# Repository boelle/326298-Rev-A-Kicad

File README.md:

Shield: [![CC BY-NC-ND 4.0][cc-by-nc-nd-shield]][cc-by-nc-nd]

This work is licensed under a [Attribution-NonCommercial-NoDerivatives 4.0 International License][cc-by-nc-nd].

[![CC BY-NC-ND 4.0][cc-by-nc-nd-image]][cc-by-nc-nd]

[cc-by-nc-nd]: http://creativecommons.org/licenses/by-nc-nd/4.0/
[cc-by-nc-nd-image]: https://licensebuttons.net/l/by-nc-nd/4.0/88x31.png
[cc-by-nc-nd-shield]: https://img.shields.io/badge/License-CC%20BY--NC--ND%204.0-lightgrey.svg

# What is this?

It's my project/attempt at recreating the first board used in C64 production.
It's based on a schematic by Ruud Baltissen.

# How?
I got one of these boards without much components, all chips where gone (almost).
I then removed the rest and cleaned out all holes and got it scanned at a local copy shop.
Initial I used sprint layout which has a feature to trace on top of an image.
But I wanted a more "complete" soloution so I imported the copper layers in to kicad and 
managed to trace on top of that. 
But the schematic was not the same as the board and I got help from Fredric QJ Blåholtz
adjustning the schematic to the board, it's a bit backwards but I trust the board more.

# Why?
I have been asked that a lot. One reason is that I have always liked the C64 and I
wanted to get more intimate with it. One thing I have truly learned is that QA and QC 
was not that much used 37 years ago, anything that worked was ok. So boards could differ 
even thou they had the same number. So I decided to just stick with making a replica of
what I had. 

The other reason is that I have a lot of time on my hands so I wanted to make
something, that at some point will come in as usefull. These boards will at some point fail.
They where not robust made 37 years ago and either a hole will break loose from the board
or a track will crack. Having a source for a new board would then come in handy. Simply
pick a PCB house that you trust and send them the gerber files. Most have a minimum order
so you will never have a problem again.

# Status?
I have verified the board by printing out the tracks on paper and used a needle to poke
through and see if things match up. It does very close but since paper under the real board
can move it will not be precise, but it's as good as I can do it.

I have also added some "eyecandy" in the form of 3d shapes of most things on the board. 
there are some things I can't find thou and my skills are not up to doing that from scratch,
but if anyone wants to chip in I need step/stp files for these parts:

# Plan?
At summer 2020 I will order 5 boards as that is the minimum from Elecrow. I will then
during fall/winter buy and add components. Since the chips are the most expensive parts,
it might be as far as early 2021 before i can power it up

# Working on right now?
Trying to locate cad/3d models in step/stp format for the missing bits

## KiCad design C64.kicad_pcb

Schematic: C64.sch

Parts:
C1, C2, C3, C16, C18, C22, C30, C31, C32, C35, C39, C45, C46, C47, C55, C56, C58, C68, C71, C74, C76, C77, C82, C84, C87, C89, C95, C96: 0.1 uF; 12_03_07
C4, C5, C6, C7, C9, C29, C33, C44, C51, C60, C85: 0.47 uF; 12_03_07
C8, C12, C13, C14, C15, C17, C24, C34, C57, C62, C64, C65, C94: 10 uF 25V; CAPACITOR_ELECTROLYTIC_2.5_6
C10, C11: 2200 pF Polyester; polyester12_03_07
C19: 2200 uF 16V; E37-31.5-17.5-E
C20, C21, C97, C98, C99, C100: 0.22 uF 100V; 0203
C23: 360 pF; 12_03_07
C25, C26, C27, C28, C40, C41, C42, C43, C50, C54, C59, C92: 0.22 uF; 12_03_07
C36: 20 pF 50V; 12_03_07
C37, C48, C93: 1000 pF; 12_03_07
C38, C80: 51 pF; 12_03_07
C49, C52: 470 pF 50V; 12_03_07
C53: 470 pF; 12_03_07
C61, C63, C66, C67: 0.47 uF 50V 20%; 15_4_10
C70: 10 pF 5%; 12_03_07
C72, C78: 220 pF 50V; 12_03_07
C73: 150 pF 50V; 12_03_07
C79: 510 pF; 12_03_07
C81: 20 pF; 12_03_07
C83: 33 pF; 12_03_07
C86: 39 pF 50V 5%; 12_03_07
C88, C90: 470 uF 50V; E37-31.5-17.5-E
C91: 100 uF 16V; C_E_5-9
C101: 0.1 uF; P5
CN1: KEYBOARD; 20way
CN2: USERPORT
CN3: CASSETTEPORT
CN4: DIN6
CN5: DIN5
CN6: EXPANSIONPORT
CN7: DIN7
CN8, CN9: CONTROL_PORT
CR1: 1N4371 2.7 V; D-12_3_7
CR2: 7.5 V; D-12_3_7
CR3: 1N914; D-12_3_7
CR4: BRIDGE_RECTIFIER
CR5, CR6: 1N4001; D-12_3_7
F1: 1A; SH32
FB1, FB2, FB3, FB4, FB5, FB6, FB7, FB8, FB9, FB10, FB11, FB12, FB13, FB14, FB15, FB16, FB17, FB18: FERRITE_BEAD
FRAME1: FRAME_D_L
J1, J2, J3: Conn_01x01; Socket_Strip_Straight_1x01_Pitch2.54mm
JP2E1: CN10; 3way
L1, L2: 2.2 uH; 12_03_07
L3: 3 uH; 12_03_07
L4: LINEFILTER
L5: 1.2 uH; P15
Q1: 2N4401; TO92
Q2: 2N3904; TO92
Q3: TIP29B
Q4, Q5, Q6, Q7, Q8: PN2222; TO92
R1, R24, R43, R44, R45: 3.3 K; 12_03_07
R2, R5, R15, R22: 1.5 K; 12_03_07
R3, R7: 10 K; 12_03_07
R4, R6, R13, R16, R23, R28, R29, R30, R31, R36, R38: 1 K; 12_03_07
R8, R39: 390; 12_03_07
R9, R26: 75; 12_03_07
R10, R11: 120; 12_03_07
R14: 100; 12_03_07
R17: 1.2 K; 12_03_07
R18: 230; 12_03_07
R19: 15 K; 12_03_07
R20, R37: 6.8 K; 12_03_07
R21: 4.7 K; 12_03_07
R25: 1 K Trim Pot; POT_METER
R27: 2 K Trim Pot; POT_METER
R33, R34: 47 K; 12_03_07
R35: 470 K; 12_03_07
R41: 1 M; 12_03_07
R42: 0; 12_03_07
R46: 2.1 K; 12_03_07
R49: 470; 12_03_07
RF1: RF-MODULATOR
RP1, RP2: 33; RESISTOR_PACK_4
RP3: 3.3 K; RESISTOR_PACK_4
RP4: 3.3 K; RESISTOR_PACK_9
SW1: DPDT_SWITCH
U1, U2: 6526
U3, U4: 2364
U5: 2332
U6: 2114
U7: 6510
U8: SN7406NN
U9, U10, U11, U12, U21, U22, U23, U24: 4164
U13, U25: SN74257N
U14: SN74258N
U15: SN74139N
U16, U28: 4066
U17: C64PLA
U18: 6581
U19: 6569
U20: 556DIGITAL
U26: SN74373N; 74373N
U27: SN7408N
U29: SN7474N
U30: SN74193N
U31: SN74629
U32: MC4044
U33: 74LS02; 7402
U34: 74LS175; SN74629
VR1: 7812; VR
VR2: 7805; VR
Y1: 17.73 MHz; HC49TL-H

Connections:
/+5Vc: C55.1, C56.1, C67.1, C68.1, C74.1, C82.1, C84.1, J1.1, L2.2, Q7.3 (C), R16.1, R23.1, R26.1, R27.E, U29.10 (PRE), U29.13 (CLR), U29.14 (VCC), U30.4 (CNT-DWN), U30.15 (A), U30.16 (VCC), U31.16 (VCC), U32.14 (VCC)
/+5Vcan: C60.1, C63.1, C64.+ (1), C65.+ (1), C66.1, C101.1, L1.1, L2.1, U19.40 (VCC), VR2.3 (VO)
/+5Vvid: C61.1, C71.1, C77.1, L1.2, Q4.3 (C), Q5.3 (C), R8.1, R13.1
/+9V: C18.1, C19.+ (1), C95.1, CR4.1 (+), CR6.1 (A), Q1.3 (C), Q3.2 (C), R2.1, VR2.1 (VI)
/+12V: C52.1, C53.1, C57.+ (1), C59.1, C62.+ (1), C94.+ (1), FB11.1, FB12.1, Q8.3 (C), VR1.3 (VO)
/A0: CN6.Y (A0), U1.38 (RS0), U2.38 (RS0), U3.8 (A0), U4.8 (A0), U5.8 (A0), U6.5 (A0), U7.7 (A0), U18.9 (A0), U25.13 (4B), U26.6 (3Q)
/A1: CN6.X (A1), U1.37 (RS1), U2.37 (RS1), U3.7 (A1), U4.7 (A1), U5.7 (A1), U6.6 (A1), U7.8 (A1), U18.10 (A1), U25.10 (3B), U26.12 (5Q)
/A2: CN6.W (A2), U1.36 (RS2), U2.36 (RS2), U3.6 (A2), U4.6 (A2), U5.6 (A2), U6.7 (A2), U7.9 (A2), U18.11 (A2), U25.6 (2B), U26.9 (4Q)
/A3: CN6.V (A3), U1.35 (RS3), U2.35 (RS3), U3.5 (A3), U4.5 (A3), U5.5 (A3), U6.4 (A3), U7.10 (A3), U18.12 (A3), U25.3 (1B), U26.15 (6Q)
/A4: CN6.U (A4), U3.4 (A4), U4.4 (A4), U5.4 (A4), U6.3 (A4), U7.11 (A4), U13.13 (4B), U18.13 (A4), U26.16 (7Q)
/A5: CN6.T (A5), U3.3 (A5), U4.3 (A5), U5.3 (A5), U6.2 (A5), U7.12 (A5), U13.6 (2B), U26.19 (8Q)
/A6: CN6.S (A6), U3.2 (A6), U4.2 (A6), U5.2 (A6), U6.1 (A6), U7.13 (A6), U13.3 (1B), U26.5 (2Q)
/A7: CN6.R (A7), U3.1 (A7), U4.1 (A7), U5.1 (A7), U6.17 (A7), U7.14 (A7), U26.2 (1Q)
/A8: CN6.P (A8), U3.23 (A8), U4.23 (A8), U5.23 (A8), U6.16 (A8), U7.15 (A8), U15.14 (A), U19.32 (A8), U25.14 (4A)
/A9: CN6.N (A9), U3.22 (A9), U4.22 (A9), U5.22 (A9), U6.15 (A9), U7.16 (A9), U15.13 (B), U19.33 (A9), U25.11 (3A)
/A10: CN6.M (A10), U3.19 (A10), U4.19 (A10), U5.19 (A10), U7.17 (A10), U15.2 (A), U19.34 (A10), U25.5 (2A)
/A11: CN6.L (A11), U3.18 (A11), U4.18 (A11), U5.18 (A11), U7.18 (A11), U15.3 (B), U19.23 (A11), U25.2 (1A)
/A12: CN6.K (A12), RP4.9 (X), U3.21 (A12), U4.21 (A12), U7.19 (A12), U13.14 (4A), U17.27 (A12)
/A13: CN6.J (A13), RP4.7 (X), U7.20 (A13), U13.5 (2A), U17.2 (A13)
/A14: CN6.H (A14), RP4.5 (X), U7.22 (A14), U13.2 (1A), U17.3 (A14)
/A15: CN6.F (A15), RP4.4 (X), U7.23 (A15), U13.11 (3A), U17.4 (A15)
/D0: CN6.21 (D0), U1.33 (D0), U2.33 (D0), U3.9 (O0), U4.9 (O0), U5.9 (O0), U7.37 (D0), U16.11 (Y3), U18.15 (D0), U19.7 (D0), U21.2 (DI), U21.14 (DO)
/D1: CN6.20 (D1), U1.32 (D1), U2.32 (D1), U3.10 (O1), U4.10 (O1), U5.10 (O1), U7.36 (D1), U9.2 (DI), U9.14 (DO), U16.8 (Y2), U18.16 (D1), U19.6 (D1)
/D2: CN6.19 (D2), U1.31 (D2), U2.31 (D2), U3.11 (O2), U4.11 (O2), U5.11 (O2), U7.35 (D2), U16.4 (Y1), U18.17 (D2), U19.5 (D2), U22.2 (DI), U22.14 (DO)
/D3: CN6.18 (D3), U1.30 (D3), U2.30 (D3), U3.13 (O3), U4.13 (O3), U5.13 (O3), U7.34 (D3), U10.2 (DI), U10.14 (DO), U16.1 (Y0), U18.18 (D3), U19.4 (D3)
/D4: CN6.17 (D4), U1.29 (D4), U2.29 (D4), U3.14 (O4), U4.14 (O4), U5.14 (O4), U7.33 (D4), U18.19 (D4), U19.3 (D4), U23.2 (DI), U23.14 (DO)
/D5: CN6.16 (D5), U1.28 (D5), U2.28 (D5), U3.15 (O5), U4.15 (O5), U5.15 (O5), U7.32 (D5), U11.2 (DI), U11.14 (DO), U18.20 (D5), U19.2 (D5)
/D6: CN6.15 (D6), U1.27 (D6), U2.27 (D6), U3.16 (O6), U4.16 (O6), U5.16 (O6), U7.31 (D6), U18.21 (D6), U19.1 (D6), U24.2 (DI), U24.14 (DO)
/D7: CN6.14 (D7), U1.26 (D7), U2.26 (D7), U3.17 (O7), U4.17 (O7), U5.17 (O7), U7.30 (D7), U12.2 (DI), U12.14 (DO), U18.22 (D7), U19.39 (D7)
/IRQ: CN6.4 (IRQ), RP4.2, U1.21 (~IRQ~), U7.3 (~IRQ~), U19.8 (~IRQ~)
/MA0: RP2.4 (2), U9.5 (A0), U10.5 (A0), U11.5 (A0), U12.5 (A0), U21.5 (A0), U22.5 (A0), U23.5 (A0), U24.5 (A0)
/MA1: RP2.8 (2), U9.7 (A1), U10.7 (A1), U11.7 (A1), U12.7 (A1), U21.7 (A1), U22.7 (A1), U23.7 (A1), U24.7 (A1)
/MA2: RP2.6 (2), U9.6 (A2), U10.6 (A2), U11.6 (A2), U12.6 (A2), U21.6 (A2), U22.6 (A2), U23.6 (A2), U24.6 (A2)
/MA3: RP2.2, U9.12 (A3), U10.12 (A3), U11.12 (A3), U12.12 (A3), U21.12 (A3), U22.12 (A3), U23.12 (A3), U24.12 (A3)
/MA4: RP1.4 (2), U9.11 (A4), U10.11 (A4), U11.11 (A4), U12.11 (A4), U21.11 (A4), U22.11 (A4), U23.11 (A4), U24.11 (A4)
/MA5: RP1.6 (2), U9.10 (A5), U10.10 (A5), U11.10 (A5), U12.10 (A5), U21.10 (A5), U22.10 (A5), U23.10 (A5), U24.10 (A5)
/MA6: RP1.2, U9.13 (A6), U10.13 (A6), U11.13 (A6), U12.13 (A6), U21.13 (A6), U22.13 (A6), U23.13 (A6), U24.13 (A6)
/MA7: RP1.8 (2), U9.9 (A7), U10.9 (A7), U11.9 (A7), U12.9 (A7), U21.9 (A7), U22.9 (A7), U23.9 (A7), U24.9 (A7)
/N$1: C12.+ (1), C35.1, U18.26 (EXT-IN)
/N$2: FB13.1, R6.1, U18.27 (AUDIO-OUT)
/N$3: FB13.2, R7.1
/N$4: C37.1, Q8.2 (B), R7.2
/N$5: C13.+ (1), Q8.1 (E), R38.1
/N$6: C10.2, U18.2 (CAP1B)
/N$7: C11.2, U18.4 (CAP2B)
/N$8: C10.1, U18.1 (CAP1A)
/N$9: C11.1, U18.3 (CAP2A)
/N$10: C13.- (2), CN5.3, RF1.AUDI (AUDIO)
/N$11: C12.- (2), CN5.5
/N$12: C34.+ (1), C50.1, FB10.1, R46.1, U18.25 (VCC)
/N$13: C16.1, FB6.2, RF1.+ (+V)
/N$14: C51.1, FB11.2, U18.28 (V12)
/N$15: C80.1, FB14.2, R25.A
/N$16: FB14.1, U19.14 (COLOR)
/N$17: C97.1, CN7.4, CN7.5, L5.1
/N$18: C100.1, L5.2, SW1.2
/N$19: C20.2, CN7.6, L4.4
/N$20: C20.1, CN7.7, L4.2
/N$21: C21.1, C98.1, F1.1A, F1.1B, L4.3
/N$22: C21.2, C99.1, L4.1, SW1.5
/N$23: CN2.11 (9VAC1), CR4.4 (AC2), F1.2A, F1.2B, R5.1
/N$24: C90.- (2), CN2.10 (9VAC2), CR4.3 (AC1), SW1.6 (O)
/N$26: C90.+ (1), CR5.1 (A), CR6.2 (C)
/N$27: C88.+ (1), C89.1, CR5.2 (C), VR1.1 (VI)
/N$28: R24.1, R25.S
/N$29: C81.2, R24.2
/N$30: C81.1, Q6.2 (B), R20.1, R21.1
/N$31: Q5.2 (B), Q6.3 (C), R13.2, R20.2
/N$32: C79.2, Q5.1 (E), R14.1
/N$33: L3.1, R10.2, R11.2, R18.1
/N$35: C54.1, FB12.2, U19.13 (V12)
/N$36: C73.1, CR3.1 (A), Q4.2 (B), R8.2
/N$37: CR3.2 (C), FB15.2
/N$38: Q4.1 (E), R9.1, R10.1
/N$39: C72.1, CN5.1, R9.2
/N$41: C78.1, CN5.4, L3.2, R49.1, RF1.VIDE (VIDEO)
/N$42: U14.10 (3B), U14.11 (3A), U19.31 (A7)
/N$44: U14.13 (4B), U14.14 (4A), U19.30 (A6)
/N$45: U14.3 (1B), U14.12 (4Y)
/N$46: U14.6 (2B), U14.9 (3Y)
/N$47: U6.14 (D0), U16.10 (Z3), U19.38 (D8)
/N$48: U6.13 (D1), U16.9 (Z2), U19.37 (D9)
/N$49: U6.12 (D2), U16.3 (Z1), U19.36 (D10)
/N$50: U6.11 (D3), U16.2 (Z0), U19.35 (D11)
/N$51: R42.2, U17.18 (CASRAM)
/N$52: U8.11 (I), U14.15 (G), U16.5 (E1), U16.6 (E2), U16.12 (E3), U16.13 (E0), U19.16 (AEC), U26.1 (OC), U27.4 (I0), U27.10 (I1)
/N$53: U8.13 (I), U13.1 (~A~/B), U14.1 (~A~/B), U17.9 (CAS), U19.19 (~CAS~), U25.1 (~A~/B)
/N$54: R42.1, U9.15 (~CAS), U10.15 (~CAS), U11.15 (~CAS), U12.15 (~CAS), U21.15 (~CAS), U22.15 (~CAS), U23.15 (~CAS), U24.15 (~CAS)
/N$55: U9.4 (~RAS), U10.4 (~RAS), U11.4 (~RAS), U12.4 (~RAS), U19.18 (~RAS~), U21.4 (~RAS), U22.4 (~RAS), U23.4 (~RAS), U24.4 (~RAS), U26.11 (ENC)
/N$56: U6.8 (~CS), U27.8 (O)
/N$59: C24.- (2), R34.2, U20.8 (TR), U20.12 (THR)
/N$60: U8.5 (I), U20.5 (Q)
/N$61: C23.1, R33.2, U20.1 (DIS), U20.2 (THR)
/N$62: C38.2, R35.1, U20.6 (TR)
/N$63: C38.1, CN1.3, R41.2
/N$64: R26.2, U31.15 (I1)
/N$65: C58.1, R27.S, U31.1 (VCO)
/N$66: FB16.1, U31.10 (Y1)
/N$67: C70.2, U31.13 (X2)
/N$68: U31.12 (X1), Y1.2
/N$69: C70.1, Y1.1
/N$70: FB16.2, U19.21 (COLCLK), U30.5 (CNT-UP)
/N$71: C83.1, U30.11 (LOAD), U30.12 (CRY)
/N$72: J3.1, U29.4 (PRE), U30.1 (C), U30.10 (B)
/N$73: U29.5 (Q), U30.9 (D)
/N$74: R16.2, R17.2, U31.2 (FREQ), U32.8 (BO)
/N$75: U29.11 (CLK), U30.6 (QC)
/N$76: U29.8 (~Q), U29.12 (D)
/N$77: U32.2 (PDO2), U32.11 (CPI2)
/N$78: U32.4 (CPI1), U32.13 (PDO1)
/N$79: C87.1, R22.1, R23.2, U31.3 (I3)
/N$80: C86.1, U31.4 (C1)
/N$81: C86.2, U31.5 (C2)
/N$82: FB17.1, U31.7 (Y2)
/N$83: U29.9 (Q), U32.1 (PDI1)
/N$84: CN3.5 (WRITE1), CN3.E (WRITE2), FB1.1
/N$85: R19.2, U32.5 (CPI3), U32.10 (CPO)
/N$86: C85.1, R17.1
/N$87: C36.1, CN6.6 (DOTCLK), FB17.2, U19.22 (DOTCLK)
/N$88: C85.2, Q7.2 (B), R19.1
/N$89: R31.2, U8.10 (O), U13.15 (G), U17.25 (AEC), U25.15 (G)
/N$90: Q7.1 (E), U32.9 (BI)
/N$91: CN1.19, CN8.2, U1.3 (PA1)
/N$92: CN1.18, CN8.3, U1.4 (PA2)
/N$93: CN1.17, CN8.4, U1.5 (PA3)
/N$94: CN1.16, CN8.6, U1.6 (PA4)
/N$95: CN1.15, U1.7 (PA5)
/N$96: CN1.14, U1.8 (PA6), U28.6 (E2), U28.12 (E3)
/N$97: CN1.20, U1.9 (PA7), U28.5 (E1), U28.13 (E0)
/N$98: CN1.13, CN8.1, U1.2 (PA0)
/N$99: CN1.12, CN9.1, U1.10 (PB0)
/N$100: CN1.11, CN9.2, U1.11 (PB1)
/N$101: CN1.10, CN9.3, U1.12 (PB2)
/N$102: CN1.9, U1.17 (PB7)
/N$103: CN1.8, CN9.6, U1.14 (PB4), U19.9 (LP)
/N$104: CN1.7, U1.15 (PB5)
/N$105: CN1.5, CN9.4, U1.13 (PB3)
/N$106: CN1.6, U1.16 (PB6)
/N$107: CN8.9, U28.1 (Y0)
/N$108: CN8.5, U28.4 (Y1)
/N$109: CN8.7, CN9.7, FB18.1
/N$110: CN9.9, U28.8 (Y2)
/N$111: CN9.5, U28.11 (Y3)
/N$113: C93.2, U18.23 (POTY), U28.3 (Z1), U28.10 (Z3)
/N$114: CN4.3, FB7.1
/N$115: CN4.4, FB9.1
/N$116: CN4.5, FB8.1
/N$117: FB8.2, R29.2, U2.9 (PA7), U8.4 (O)
/N$118: FB9.2, R30.2, U2.8 (PA6), U8.8 (O)
/N$119: CN2.9 (ATN), FB7.2, R28.2, U8.2 (O)
/N$120: CN2.8 (PC2), U2.18 (~PC~)
/N$121: CN2.L (PB7), U2.17 (PB7)
/N$122: CN2.K (PB6), U2.16 (PB6)
/N$123: CN2.J (PB5), U2.15 (PB5)
/N$124: CN2.H (PB4), U2.14 (PB4)
/N$125: CN2.F (PB3), U2.13 (PB3)
/N$126: CN2.E (PB2), U2.12 (PB2)
/N$127: CN2.D (PB1), U2.11 (PB1)
/N$128: CN2.C (PB0), U2.10 (PB0)
/N$129: CN2.B (FLAG2), RP3.2, U2.24 (~FLAG~)
/N$130: U2.7 (PA5), U8.3 (I)
/N$131: U2.6 (PA4), U8.9 (I)
/N$132: U2.5 (PA3), U8.1 (I)
/N$133: CN3.3 (MOTOR1), CN3.C (MOTOR2), FB2.1
/N$134: CN2.4 (CNT1), RP3.5 (X), U1.40 (CNT)
/N$135: U2.2 (PA0), U14.2 (1A), U17.5 (VIA14)
/N$136: U2.3 (PA1), U14.5 (2A)
/N$137: CN2.M (PA2), U2.4 (PA2)
/N$138: CN2.7 (SP2), RP3.8 (X), U2.39 (SP)
/N$139: CN2.6 (CNT2), RP3.7 (X), U2.40 (CNT)
/N$140: CN2.5 (SP1), RP3.6 (X), U1.39 (SP)
/N$141: FB5.1, U7.39 (CLKOUT)
/N$143: C76.1, R15.1, U31.14 (RNG)
/N$145: U3.20 (CS), U17.17 (BASIC)
/N$146: CR1.2 (C), R5.2, R37.2, U27.12 (I0)
/N$147: R37.1, U1.19 (TOD), U2.19 (TOD), U27.11 (O)
/N$148: JP2E1.1, JP2E1.3, R39.2; also elsewhere on the board
/N$152: U4.20 (CS), U17.16 (KERNAL)
/N$153: CN6.C (RESET), FB4.1
/N$155: CN6.12 (BA), U17.26 (BA), U19.12 (BA), U27.1 (I0), U33.2 (I1), U33.12 (I1)
/N$157: CN6.11 (ROML), U17.11 (ROML)
/N$158: CN6.B (ROMH), U17.10 (ROMH)
/N$159: CN6.9 (EXROM), RP4.8 (X), U17.23 (EXROM)
/N$160: CN6.8 (GAME), RP4.6 (X), U17.22 (GAME)
/N$162: FB15.1, U19.15 (SYNC)
/N$163: U15.4 (Y0), U19.10 (~CS~)
/N$164: R45.2, U7.29 (P0), U17.8 (LORAM)
/N$165: R44.2, U7.28 (P1), U17.7 (HIRAM)
/N$166: R43.2, U7.27 (P2), U17.6 (CHAREN)
/N$167: U7.2 (RDY), U27.3 (O)
/N$168: U7.5 (AEC), U27.6 (O)
/N$169: CN6.13 (DMA), RP4.10 (X), U27.2 (I1), U27.5 (I1)
/N$170: U5.20 (CS1), U17.15 (CHAROM)
/N$171: CN3.4 (READ1), CN3.D (READ2), CN4.1, RP3.4 (X), U1.24 (~FLAG~)
/N$172: CN3.6 (SENSE1), CN3.F (SENSE2), R1.2, U7.25 (P4)
/N$173: C1.1, CN3.2 (VCC1), CN3.B (VCC2), FB3.1
/N$176: FB1.2, U7.26 (P3)
/N$177: Q2.2 (B), R3.1, R4.2
/N$178: Q1.1 (E), Q3.1 (B)
/N$179: C18.2, CR2.2 (C), Q1.2 (B), Q2.3 (C), R2.2
/N$180: FB2.2, Q3.3 (E)
/N$181: R4.1, U7.24 (P5)
/N$182: U1.23 (~CS~), U15.12 (Y0)
/N$183: U2.23 (~CS~), U15.11 (Y1)
/N$184: U6.10 (~WE), U17.13 (GR/W)
/N$185: U15.1 (G), U17.12 (I/O)
/N$186: U15.7 (Y3), U15.15 (G)
/N$187: CN6.7 (IO1), U15.10 (Y2)
/N$188: CN6.10 (IO2), U15.9 (Y3)
/N$189: U15.5 (Y1), U18.8 (CS)
/N$190: U15.6 (Y2), U27.9 (I0)
/NA0: RP2.3 (1), U19.24 (A0/A8), U25.12 (4Y), U26.7 (3D)
/NA1: RP2.7 (1), U19.25 (A1/A9), U25.9 (3Y), U26.13 (5D)
/NA2: RP2.5 (1), U19.26 (A2/A10), U25.7 (2Y), U26.8 (4D)
/NA3: RP2.1, U19.27 (A3/A11), U25.4 (1Y), U26.14 (6D)
/NA4: RP1.3 (1), U13.12 (4Y), U17.20 (VA12), U19.28 (A4/A12), U26.17 (7D)
/NA5: RP1.5 (1), U13.7 (2Y), U17.21 (VA13), U19.29 (A5/A13), U26.18 (8D)
/NA6: RP1.1, U13.4 (1Y), U14.4 (1Y), U26.4 (2D)
/NA7: RP1.7 (1), U13.9 (3Y), U14.7 (2Y), U26.3 (1D)
/NMI: CN6.D (NMI), RP3.3 (X), U2.21 (~IRQ~), U7.4 (~NMI~), U8.6 (O)
/PHI0: U7.1 (CLKIN), U19.17 (PHI0), U32.3 (PDI2), U33.5 (I1)
/PHI2: CN6.E (PHI2), FB5.2, U1.25 (CLKOUT), U2.25 (CLKOUT), U18.6 (CLKOUT)
/RES: CN2.3 (RESET), CN4.6, FB4.2, R36.2, U1.34 (~RES~), U2.34 (~RES~), U7.40 (~RES~), U18.5 (RESET), U20.9 (Q), U20.13 (DIS)
/RW: CN6.5 (R/W), R46.2, RP4.3 (X), U1.22 (R/W), U2.22 (R/W), U7.38 (R/W), U9.3 (~WE), U10.3 (~WE), U11.3 (~WE), U12.3 (~WE), U17.24 (R/W), U18.7 (R/W), U19.11 (~R/W~), U21.3 (~WE), U22.3 (~WE), U23.3 (~WE), U24.3 (~WE)
/VCC: C2.1, C3.1, C4.1, C5.1, C6.1, C7.1, C8.+ (1), C9.1, C14.+ (1), C15.+ (1), C17.+ (1), C22.1, C24.+ (1), C25.1, C26.1, C27.1, C28.1, C29.1, C30.1, C31.1, C32.1, C33.1, C39.1, C40.1, C41.1, C42.1, C43.1, C44.1, C45.1, C46.1, C47.1, C49.1, C91.+ (1), C92.1, C96.1, CN1.4, CN2.2 (VCC), CN6.2 (+5V1), CN6.3 (+5V2), FB3.2, FB6.1, FB10.2, FB18.2, R1.1, R28.1, R29.1, R30.1, R31.1, R33.1, R35.2, R36.1, R39.1, R41.1, R43.1, R44.1, R45.1, RP3.1, RP4.1, SW1.3 (O), U1.20 (VCC), U2.20 (VCC), U3.24 (VCC), U4.24 (VCC), U5.21 (CS2), U5.24 (VCC), U6.18 (VCC), U7.6 (VCC), U8.14 (VCC), U9.8 (VCC), U10.8 (VCC), U11.8 (VCC), U12.8 (VCC), U13.16 (VCC), U14.16 (VCC), U15.16 (VCC), U16.14 (VCC), U17.28 (VCC), U20.4 (R), U20.10 (R), U20.14 (VCC), U21.8 (VCC), U22.8 (VCC), U23.8 (VCC), U24.8 (VCC), U25.16 (VCC), U26.20 (VCC), U27.13 (I1), U27.14 (VCC), U28.14 (VCC), U33.14 (VCC), U34.16
unnamed: C79.1, R18.2
unnamed: U33.1 (I0), U34.1 (~Mr), U34.4 (D0)
unnamed: U33.4 (I0), U33.9 (I1), U34.9 (Cp)
unnamed: U33.11 (O), U34.11 (~Q2)
unnamed: U33.8 (O), U33.13 (I0)
unnamed: U34.2 (Q0), U34.5 (D1)
unnamed: U34.7 (Q1), U34.12 (D2)

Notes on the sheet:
Based on schematic done by Ruud Baltissen. Values and footprints corrected by Bo Herrmannsen Help with correcting schematic to match board by Fredric QJ Blåholtz
20-02-2018
Commodore C64 Rev A Replica Schematic
? Ends blind on board

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
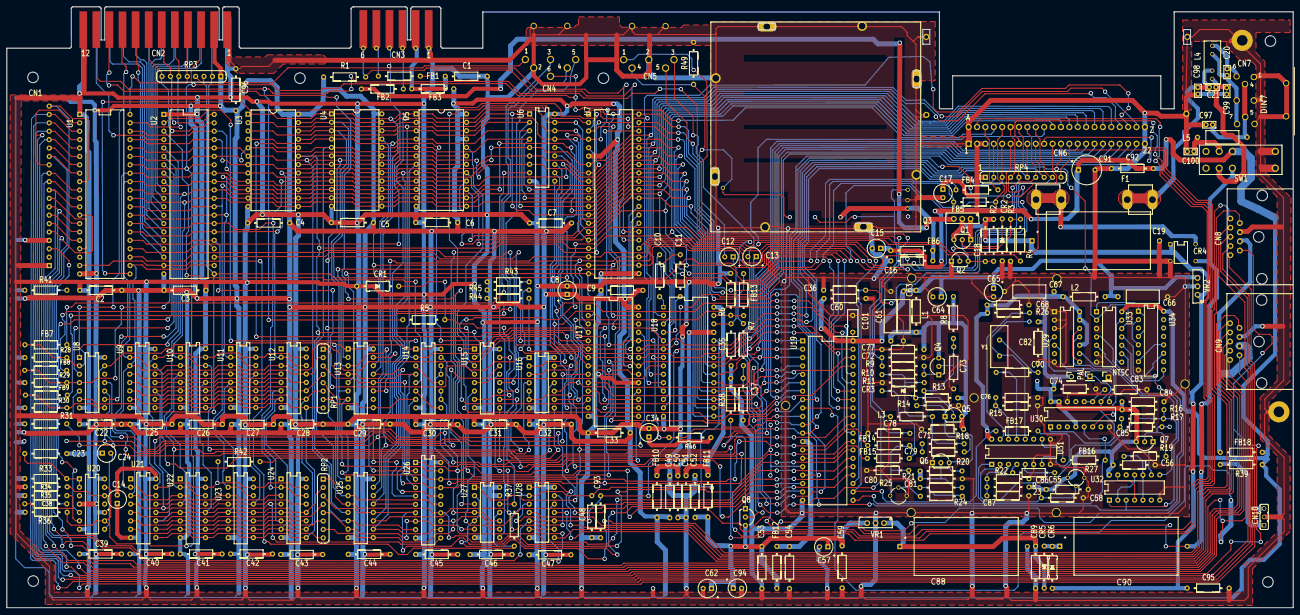
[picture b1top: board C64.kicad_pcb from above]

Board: 2 copper layers, 389.2 x 181.8 mm, 237 parts (0 on the bottom side), 234 nets.

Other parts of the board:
CN10: JP2E; 3way

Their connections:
/N$148: CN10.1, CN10.3; also elsewhere on the board

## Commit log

2018-02-24 initial push after split up
2018-02-25 added ground and vcc fill area's
    also adjusted a bit on schematic to make it match board
2018-02-26 cleaned up the outer edge
2018-02-26 more adjustment to schematic
    ~56 unconnected left. most inside the vic area
2018-02-26 a few more adjustmenst
    ~55 unconnected left
2018-02-26 last updates etc
    Time to take a break :-D
2018-02-27 corrections on transistors for casseste control
2018-02-27 forgot one track to userport
2018-02-27 fixed track at RP4
2018-02-27 C34 cahnged to 5v can
2018-02-27 4 connections left
    There should be a via under R46 but the 2 traks that cross each other does not have the same name
    Have checked the RES line and it all seems to connect, there must be a microscopic disconnect somewhere on the RES line
    Next step is to import all holes on one of the user layers and check that all via's are there
2018-02-28 2 connections left
    C34 and Via under R46 is the mystery
    will need to check that all via's are in place, one missing and it can fail
2018-02-28 added all via's from sprint layout proram on F.adhes layer
    since this will be hand assembly i'm not going to need adhesion/glue
    this will be used to check that all via's are there and it will also be used for fine adjusting placements etc
2018-02-28 corrected a few more things
    Thanks to Fredric QJ Blåholtz for the help so far
2018-02-28 added u33 and u34 on schematic
    these needs to be wired by the tracks on the board. no schematic found with them wired in
2018-02-28 added schematic symbols for U33 and U34
    u33 needs some edit work before connections in schematic can be made
2018-03-01 added 2 missing ic's
    these are for NTSC versions
2018-03-01 added 3d shapes to ntsc chips
2018-03-01 all tracks connected. Hurra :-D
2018-03-01 minor corrections to casette port footprint
2018-03-01 minor corrections
2018-03-01 more adjustments
2018-03-01 minor adjustments to userport
    pad 1+2 done and pads 10+11 (and their counterparts on the other side of board)
2018-03-02 first adjustments on silk screen
2018-03-02 recreated edge cut
2018-03-02 outline done
    missing is milling on RF modulator and adjusting control ports and power input
2018-03-03 more footprints and schematic corrections
    a lot of the schematic symbols was still from the eagle import and pcb footprints had not been saved as individual footprints
2018-03-03 negative copper layers back
    will use them to adjust thickness etc
2018-03-03 more supply symbols
    All symbols on schematic should now be saved as individual lib's
2018-03-03 most supply tracks
    supply tracks roughly in place. a few is missing and they all need to be fine adjusted later
2018-03-04 more supply tracks done
2018-03-05 removed solder mask on front side
2018-03-05 removed dwgs.user from userport
    makes it look strange in 3d view
2018-03-06 more "polising"
    added blind ending track at FB12
2018-03-06 a few corrections on references
    Commodore placed the references for C98 and C99 wrong, have made them switch place.
    C53 and C54 the same thing.
2018-03-07 first adjustmens to userport
    Total width is now correct
    pads are correct but they will need to be moved as a group later on
2018-03-07 last correction to userport
2018-03-07 first adjust on tape port
2018-03-07 tape port done
    to come is spacing from top left corner to user port and spacing between userport and tape port
2018-03-07 big cleanup
2018-03-07 ic 3d shapes folder added
2018-03-07 removed old drill layer info
    this was used to place components more precise and is no longer needed
2018-03-08 silk screen 1#2
    left half of board done
2018-03-08 silk screen 1½#2
    real life happens for even the best of us. back later to do the last bit
2018-03-08 silk screen 2#2
2018-03-08 c54 & 53 corrected
2018-03-10 added fuse to 3d view
2018-03-13 added silkscreen on c101 and Y1
    also checked userport and casette port. they seem to be spaced correctly from top left corner and the spacing between them also seems ok. expansion port is also the correct distance from top right co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
2018-03-18 minor updates
2018-03-20 cleared b-adhes
    it was the old silk screen
2018-06-18 added resistors with color rings
2018-08-04 update to 3d resistor
2019-01-17 added more 3d shapes
    also added vic area frame and exp. port bracket
2019-01-18 correcting spelling mistakes
2019-01-20 added logo's
    need to move them from eco1 layer to copper
2019-01-21 added logo to back side
2019-01-22 gerbers generated
2019-02-08 hiden eco layers
2019-12-30 more 3d
    and board edge
2020-01-26 Winter cleanup
2020-06-16 bigger holes
2020-06-20 updated gerbers
2020-07-02 Create LICENSE
2020-07-02 Update LICENSE
2020-08-24 expansion port pads improved
2020-10-03 octogon expansion port pads
2021-04-29 version update
    just updating to (5.1.6)-1 of eeschema
